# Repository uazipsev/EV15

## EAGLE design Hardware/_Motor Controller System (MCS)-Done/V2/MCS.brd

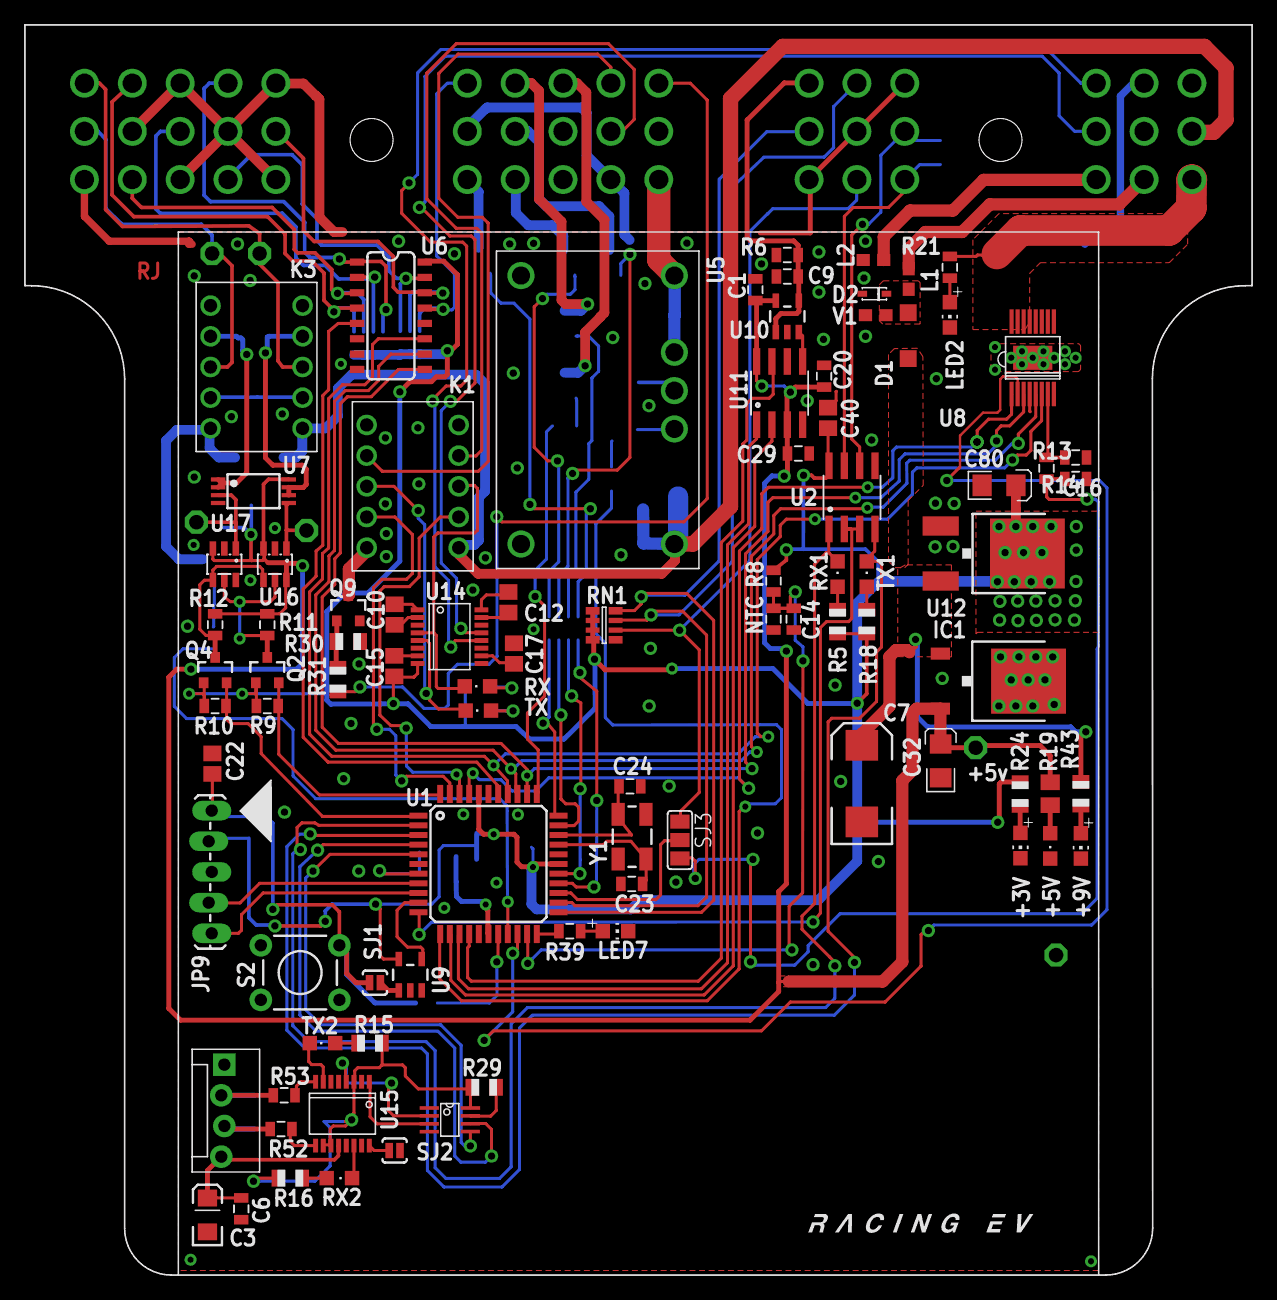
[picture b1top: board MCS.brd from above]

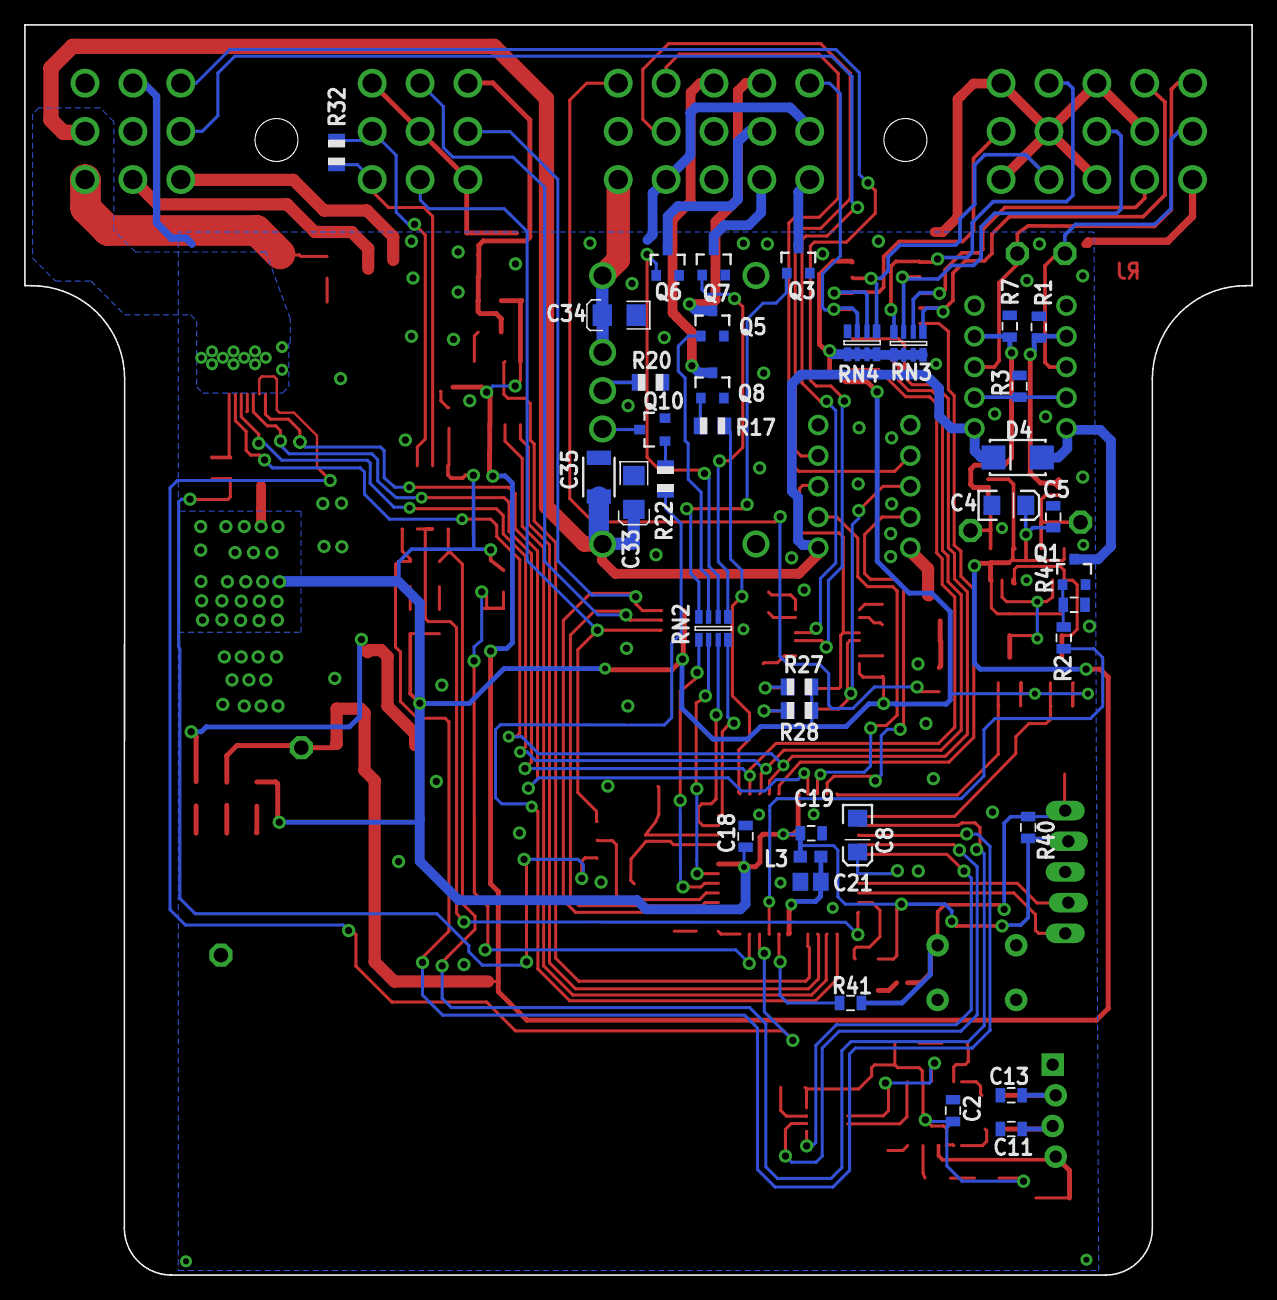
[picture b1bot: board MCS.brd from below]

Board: 2 copper layers, 101.6 x 103.5 mm, 133 parts (37 on the bottom side), 126 nets.

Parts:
+3V, +9V: CHIP-LED0805
+5V: Green; CHIPLED_0805
C1, C5, C14, C18, C19, C20, C29: 0.1uF; 0805
C2, C6: 0.1uf; 0805
C3: 4.7uF; EIA3216
C4, C8: 10uF; EIA3216
C7: 100uF; EIA7343
C9, C16: 10pF; 0805
C10, C12, C15, C17, C40: .1uF; C0805
C11, C13: 47pf; 0805
C21: 100n; C0805
C22: 10n; C0805
C23, C24: 12pF; 0805
C32, C33, C34, C80: 10uF; POLC1206
C35: 1uf; 1210
CASE2: 581-01-48-009
D1: 1N4001; SOD123
D2: MM5Z30; SOD-523F
D4: SMA-DIODE_ALT
IC1: 7805DT; TO252
JP9: ICSP; 1X05_LOCK_LONGPADS
JP13: MOLEX-1X4_LOCK
K1, K3: TQ2-2M-24V
L1, L2, L3: FB; 0603
LED2, LED7: CHIP-LED0805
NTC: 0805
Q1, Q2, Q3, Q4, Q5, Q6, Q7, Q8, Q9, Q10: BSS123; SOT23-3
R1, R6, R7, R8, R11, R12, R13, R14, R40: 10k; 0805
R2: 1k; 0805
R3: 100; 0805
R4: 100k; 0805
R5, R15, R17, R22, R27, R29, R31: 1K; R0805
R9, R10: 2k; 0805
R16, R18, R28: 1k; R0805
R19: 1K; M0805
R20: 383k; R0805
R21: 3.3k; 0805
R24: 499; R0805
R30: 10K; R0805
R32: 120; R0805
R39, R41: 499; 0805
R43: 1.2k; R0805
R52, R53: 27; 0805
RN1, RN2, RN3, RN4: RN-4; CRA06S
RX, RX2: CHIPLED_0805
RX1: RED; CHIPLED_0805
S2: ts; TACTILE-PTH
SJ1: SJ-NO; SJ_2S-NO
SJ2: PAD-JUMPER-2-NO_YES_SILK
SJ3: PAD-JUMPER-3-NO_YES_SILK_FULL_BOX
TP1, TP2, TP3, TP4, TP5, TP8: TESTPOINT; 4952
TX, TX2: CHIPLED_0805
TX1: GREEN; CHIPLED_0805
U1: DSPIC33FJ128GP804; TQFP-44
U2: SN75HVD08DR; SO-8
U4: SN74LVC2G241DCTR; VFSOP-8
U5: PTN78060HAH
U6: SN74HC251_SMD; SO016
U7: LM158; TSSOP-08
U8: VND7040AJTR-E; SSO-16-POWER
U9: MAX823; SOT23-5L
U10: OPA344; SOT23-5
U11: X9015_DIGI_POTS; SO08
U12: NCP1117DT33T5G; V-REG_DPACK
U14: ADM3101E; SSOP-16
U15: FT230X; SSOP-16
U16, U17: MCP4725; SOT23-6
U$1: LOGOM; L-M
U$2: INDPK1; PICKIT-PIN-1
V1: 13Vdc; 0603
Y1: 12Mhz; CRYSTAL-SMD-5X3

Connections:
3V: C2.1, R15.2, R16.2, R29.2, U4.8, U15.3, U15.10, U15.11
12V-EN: R22.1, U1.12
!CS: U1.15, U11.7
!RST: U1.20, U8.2
+: CASE2.45, L1.1
+3V3: C15.2, C18.1, C19.1, C40.1, C80.1, JP9.2, L3.2, Q2.1, Q4.1, R5.2, R8.2, R9.2, R10.2, R18.2, R24.2, R27.2, R28.2, R40.2, RN1.1, RN1.2, RN1.3, RN1.4, RN3.5, RN3.6, RN3.7, RN3.8, RN4.6, RN4.7, RN4.8, U1.28, U1.40, U2.8, U6.16, U9.5, U12.4, U14.8
+5V: C1.1, C4.A, C5.1, C20.1, C29.1, C32.1, IC1.2, R11.2, R12.2, R19.1, TP2.P$1, U7.8, U10.5, U11.3, U11.8, U16.3, U16.6, U17.3
+9V: C7.A, D1.C, IC1.1, R43.2, U12.3
+12V: C34.1, CASE2.30, U5.5, U5.6
+24V: C33.1, C35.1, CASE2.47, D4.C, K1.1, K3.1, U5.2, U8.EP
-: CASE2.42, L2.1
A: U1.37, U6.11, U8.6
ASEN: C16.1, R14.2, SJ3.3
B: U1.36, U6.10, U8.5
BOX_TEMP: C14.1, NTC.2, R8.1, U1.21
C: U1.35, U6.9, U8.3
DAC-EN: R2.2, U1.19
FAN: CASE2.48, R21.2, U8.13, U8.14, U8.15, U8.16
FAN-PWM: U1.41, U8.1
GND: +3V.C, +5V.C, +9V.C, C1.2, C2.2, C3.C, C4.C, C5.2, C6.2, C7.C, C8.C, C9.2, C11.2, C13.2, C14.2, C16.2, C17.1, C18.2, C19.2, C20.2, C21.2, C22.2, C23.2, C24.2, C29.2, C32.2, C33.2, C34.2, C35.2, C40.2, C80.2, CASE2.3, CASE2.5, CASE2.7, CASE2.9, CASE2.11, CASE2.13, CASE2.15, CASE2.17, CASE2.27, CASE2.33, CASE2.35, CASE2.37, CASE2.43, D2.A, IC1.3, JP9.3, JP13.1, L2.2, LED2.C, LED7.C, NTC.1, Q1.2, Q3.2, Q5.2, Q6.2, Q7.2, Q8.2, Q9.2, Q10.2, R1.2, R3.2, R4.1, R6.1, R7.2, R13.1, R20.1, R30.2, S2.1, SJ2.1, TP1.P$1, U1.6, U1.16, U1.29, U1.39, U2.5, U4.1, U4.4, U5.1, U5.7, U6.7, U6.8, U7.4, U8.4, U9.2, U10.2, U11.4, U11.6, U12.1, U14.9, U15.5, U15.13, U16.2, U17.2, U17.6, V1.1
INC: U1.14, U11.1
MC1-B: RN2.3, U1.32
MC1-F: RN2.1, U1.26
MC1-PE: RN2.4, U1.33
MC1-R: RN2.2, U1.27
MC1-RE: R17.1, U1.34
MC-1-B: CASE2.2, K3.8, TP4.P$1
MC-1-T: CASE2.1, K3.3, TP5.P$1
MC-PG-EN: CASE2.28, R31.1
MCRX: K1.3, RX.C, U14.4
MCTX: K1.8, TX.C, U14.5
unnamed: C22.1, JP9.1, R40.1, R41.1, S2.3, SJ1.2
unnamed: C21.1, L3.1, U1.17
unnamed: K3.7, R1.1, U7.1, U7.2
unnamed: C8.A, U1.7
unnamed: R39.2, U1.22
unnamed: +9V.A, R43.1
unnamed: Q3.1, RN2.8
unnamed: R41.2, U1.18
unnamed: CASE2.18, Q3.3
unnamed: SJ1.1, U9.1
unnamed: R15.1, TX2.A
unnamed: JP9.4, U1.8
unnamed: TX2.C, U15.7
unnamed: RX2.C, U15.14
unnamed: JP9.5, U1.9
unnamed: R16.1, RX2.A
unnamed: TP3.P$1, U7.5, U16.1
unnamed: K3.4, R7.1, U7.6, U7.7
unnamed: U4.2, U15.4
unnamed: Q5.1, RN2.7
unnamed: K3.2, K3.9, R3.1
unnamed: TP8.P$1, U7.3, U17.1
unnamed: LED2.A, R21.1
unnamed: U10.3, U11.5
unnamed: +3V.A, R24.1
unnamed: CASE2.19, Q5.3
unnamed: U4.3, U15.1
unnamed: R52.2, U15.9
unnamed: Q6.1, RN2.6
unnamed: CASE2.20, Q6.3
unnamed: R18.1, TX1.A
unnamed: R5.1, RX1.A
unnamed: SJ3.2, U1.25
unnamed: Q8.1, R17.2
unnamed: LED7.A, R39.1
unnamed: C24.1, U1.31, Y1.3
unnamed: C23.1, U1.30, Y1.1
unnamed: +5V.A, R19.2
unnamed: Q1.1, R2.1, R4.2
unnamed: D4.A, K3.10, Q1.3
unnamed: R13.2, R14.1, U8.7
unnamed: R53.2, U15.8
unnamed: C11.1, JP13.3, R52.1
unnamed: C10.1, U14.1
unnamed: C13.1, JP13.2, R53.1
unnamed: SJ2.2, U15.16
unnamed: D1.A, D2.C, L1.2, V1.2
unnamed: C10.2, U14.2
unnamed: C12.1, U14.16
unnamed: C12.2, U14.15
unnamed: C15.1, U14.7
unnamed: R29.1, U4.7
unnamed: CASE2.21, Q7.3
unnamed: CASE2.22, Q8.3
unnamed: C17.2, U14.10
unnamed: CASE2.40, U14.12
unnamed: CASE2.41, U14.13
unnamed: R27.1, RX.A
unnamed: R28.1, TX.A
unnamed: K1.10, Q9.3
unnamed: Q9.1, R30.1, R31.2
unnamed: R20.2, U5.4
unnamed: Q10.3, U5.3
unnamed: Q7.1, RN2.5
unnamed: Q10.1, R22.2
unnamed: C3.A, C6.1, JP13.4, U15.12
OUT: U1.38, U6.5
OUT-RX: CASE2.26, K1.4
OUT-TX: CASE2.25, K1.7
PUMP_OUTPUT_CONTROL: C9.1, CASE2.31, R6.2, U10.1, U10.4
RS-A: CASE2.38, R32.1, U2.6
RS-B: CASE2.39, R32.2, U2.7
RX2: K1.2, U1.42
RX3: U1.4, U4.6
RXD1: RX1.C, U1.2, U2.1
SCL: Q2.2, R9.1, U1.44
SCL_5V: Q2.3, R11.1, U16.5, U17.5
SDA: Q4.2, R10.1, U1.1
SDA_5V: Q4.3, R12.1, U16.4, U17.4
SP1: CASE2.4, RN3.1, U6.4
SP2: CASE2.6, RN3.2, U6.3
SP3: CASE2.8, RN3.3, U6.2
SP4: CASE2.10, RN3.4, U6.1
SP5: CASE2.12, RN4.1, U6.15
SP6: CASE2.14, RN4.2, U6.14
SP7: CASE2.16, RN4.3, U6.13
TEMP1: CASE2.32, RN1.8, U1.23
TEMP2: CASE2.34, RN1.7, U1.24
TEMP3: CASE2.36, RN1.6, SJ3.1
TX2: K1.9, U1.43
TX3: U1.5, U4.5
TXD1: TX1.C, U1.3, U2.4
U5-RE/DE: U1.11, U2.2, U2.3
UP/!DN: U1.13, U11.2
WDI: U1.10, U9.4

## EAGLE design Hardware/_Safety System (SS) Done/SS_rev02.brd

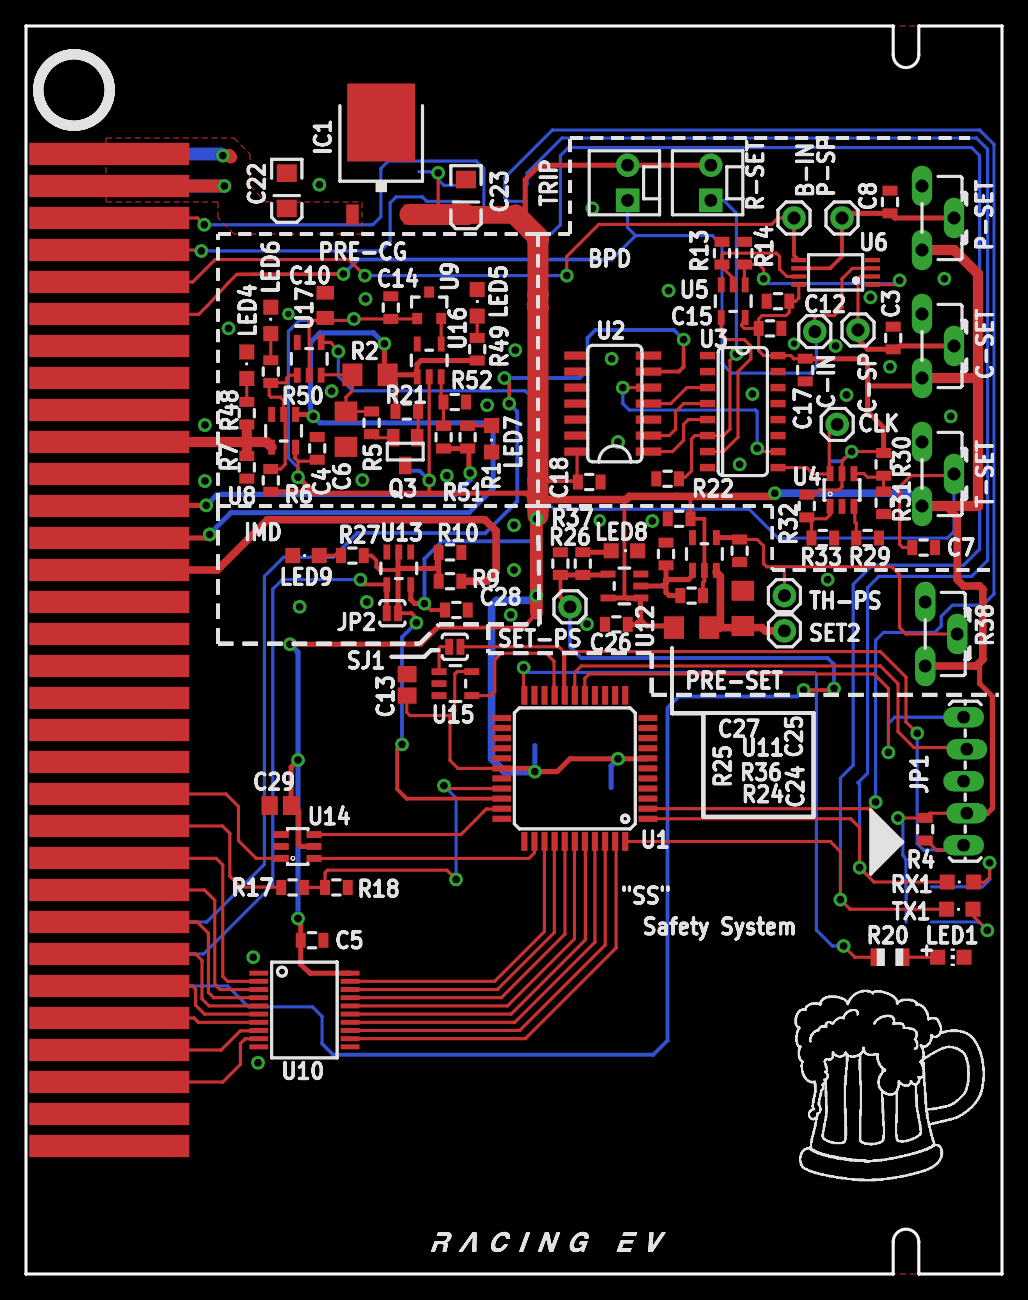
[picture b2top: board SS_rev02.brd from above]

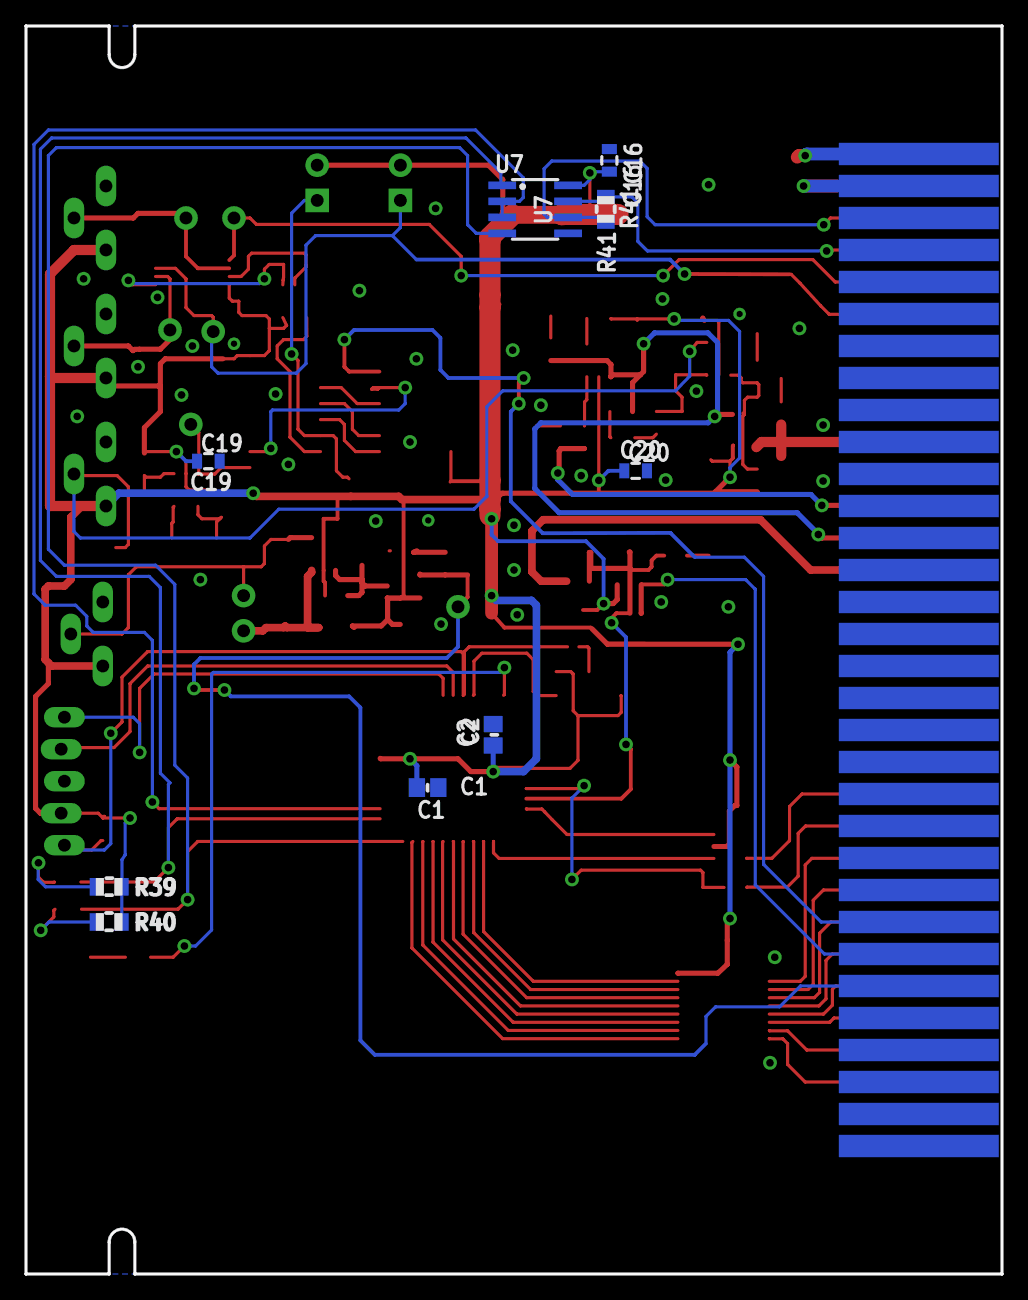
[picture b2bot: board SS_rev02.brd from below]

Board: 2 copper layers, 77.5 x 99.1 mm, 109 parts (9 on the bottom side), 78 nets.

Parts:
B-IN: TP; 1X01
C1, C2: .1uF; C0805
C3, C5, C7, C8, C20, C25: 1.0uF; 0805
C4, C14, C16, C26, C27, C28: 0.1uF; 0805
C6, C24: 100uF; 1206
C10: 0.1uF; C0805K
C12, C15, C17, C18, C19: 0.1uf; 0805
C13, C29: 0.1uF; C0805
C22, C23: 10uF; EIA3216
C-IN: TP; 1X01
C-SP: TP; 1X01
CARD1: CARD; CARD-64
CLK: TP; 1X01
IC1: 7805DT; TO252
JP1: 1X05_LOCK_LONGPADS
JP2: SJ_2S-NO
JP11: BPR; MOLEX-1X2_LOCK
JP21: Trigger; MOLEX-1X2_LOCK
LED1: CHIP-LED0805
LED4, LED5, LED6, LED7, LED8, LED9: CHIPLED_0805
P-SP: TP; 1X01
Q3: MMBT4403; SOT23
R1, R26, R48, R49: 2.0k; 0805
R2, R24: 115k; 1206
R3, R11, R12, R38: CA6H
R4, R13, R14, R18, R22: 10k; 0805
R5: 5; 0805
R6, R7, R25, R36, R37: 2.7k; 0805
R9, R10: 5k; 0805
R17: 22k; 0805
R20, R40: 1k; R0805
R21, R27, R32, R33: 1k; 0805
R29: 92k 1%; 0805
R30: 976k 1%; 0805
R31: 182k 1%; 0805
R39: 1K; R0805
R41: 120; R0805
R50: 1.0k; 0805
R51: 20k; 0805
R52: 28k; 0805
RX1: RED; CHIPLED_0805
SET2: RC-PS; 1X01
SET-PS: TP; 1X01
SJ1: SJ_2S-NO
TH-PS: TP; 1X01
TX1: GREEN; CHIPLED_0805
U1: PIC18F45K22; TQFP-44
U2: SN74HC21DR; SO14
U3: CD4015BM96; SO-16
U4: LTC6991; TSOT-23-6
U5: NC7SZ08P5X; SOT23-5
U6: LM358; TSSOP-8
U7: SN75HVD08DR; SO-8
U8: SN74AHC1G08; SOT23-5
U9: ISL21080; SOT-23
U10: MAX6818; SSOP-20
U11, U16, U17: MCP6541T-E/OT; SOT23-5
U12: SN74LVC1G132DBVR; SOT23-5
U13: NC7S14M5X; SOT23-5
U14: MAX6817EUT+T; SOT23-6
U15: MAX823; SOT23-5L
U$1: INDPK1; PICKIT-PIN-1
U$2: BEERM; B-M
U$3: LOGOM; L-M

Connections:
+5V: C1.1, C2.1, C4.1, C5.1, C10.1, C12.1, C13.1, C14.1, C15.1, C16.1, C17.1, C18.1, C19.1, C20.1, C23.A, C26.1, C27.1, C28.1, C29.1, IC1.2, JP1.2, JP11.2, JP21.2, R3.E, R4.2, R6.2, R11.E, R12.E, R24.1, R30.2, R32.2, R36.2, R38.E, R39.2, R40.2, U1.7, U1.28, U2.14, U3.16, U4.5, U5.5, U6.8, U7.8, U8.5, U9.1, U10.20, U11.2, U12.1, U12.5, U13.5, U14.5, U15.5, U16.2, U17.2
+9V: C22.A, CARD1.1, CARD1.2, CARD1.33, CARD1.34, IC1.1
AMD: CARD1.28, U10.7
AMD_O: U1.41, U10.14
AUX_O: U1.32, U14.4
BOTS: CARD1.29, U10.8
BOTS_O: U1.42, U10.13
BPD: CARD1.23, U10.2
BPD-R-SET: CARD1.57, U2.6
BPD_O: U1.36, U10.19
BRAKE_PRESURE: B-IN.1, CARD1.5, U6.5
CURRENT_SENSOR: C-IN.1, CARD1.6, JP21.1, U6.3
ECU: CARD1.30, U10.9
ECU_O: U1.43, U10.12
GND: C1.2, C2.2, C3.2, C4.2, C5.2, C6.2, C7.2, C8.2, C10.2, C12.2, C13.2, C14.2, C15.2, C16.2, C17.2, C18.2, C19.2, C20.2, C22.C, C23.C, C24.2, C25.2, C26.2, C27.2, C28.2, C29.2, CARD1.31, CARD1.32, CARD1.63, CARD1.64, IC1.3, JP1.3, LED1.C, LED4.C, LED5.C, LED6.C, LED7.C, LED8.C, LED9.C, Q3.3, R3.A, R7.1, R10.1, R11.A, R12.A, R13.2, R14.2, R18.1, R22.1, R25.1, R29.2, R31.1, R33.1, R37.1, R38.A, R52.2, U1.6, U1.29, U2.7, U3.8, U4.2, U5.3, U6.4, U7.5, U8.3, U9.3, U10.1, U10.10, U11.5, U12.3, U13.3, U14.2, U15.2, U16.5, U17.5
IMD: CARD1.24, U10.3
IMD-R-SET: CARD1.58, JP2.1, U13.4
IMD-SIG: CARD1.14, R9.2
IMD_O: U1.37, U10.18
IMD_STAT: JP2.2, R9.1, R10.2, R27.2, U1.31, U13.2
IS_O: R17.1, R18.2, U1.30
MAIN: CARD1.10, R7.2, R48.2, U8.4
unnamed: SJ1.1, U15.1
unnamed: CARD1.22, R17.2
unnamed: C25.1, R38.S, TH-PS.1, U11.4
unnamed: Q3.1, R21.2
unnamed: Q3.2, R5.1
unnamed: U2.5, U3.10
unnamed: C7.1, R3.S, U17.4
unnamed: R30.1, R31.2, U4.4
unnamed: U9.2, U16.4
unnamed: R51.2, R52.1, U16.3
unnamed: U3.7, U5.4
unnamed: JP11.1, R22.2, U3.6
unnamed: C24.1, R24.2, SET2.1, U11.3
unnamed: LED1.A, R20.1
unnamed: U2.1, U3.5
unnamed: U2.2, U3.4
unnamed: U2.4, U3.3
unnamed: R20.2, U1.22
unnamed: R29.1, U4.3
unnamed: CLK.1, U3.9, U4.6
unnamed: C8.1, P-SP.1, R12.S, U6.6
unnamed: R25.2, R36.1, U11.1, U12.2
unnamed: R32.1, R33.2, U4.1
unnamed: C3.1, C-SP.1, R11.S, U6.2
unnamed: R14.1, U5.1, U6.1
unnamed: LED8.A, R26.1
unnamed: R13.1, U5.2, U6.7
unnamed: LED9.A, R27.1
unnamed: LED7.A, R1.1
unnamed: R40.1, TX1.A
unnamed: JP1.4, U1.17
unnamed: R39.1, RX1.A
unnamed: JP1.5, U1.16
unnamed: JP1.1, R4.1, SJ1.2, U1.18
unnamed: C6.1, R2.2, R5.2, U17.3
unnamed: R6.1, R50.2, U8.2, U17.1
unnamed: LED4.A, R48.1
unnamed: LED5.A, R49.1
unnamed: LED6.A, R50.1
RELAY-SET: CARD1.59, R26.2, R37.2, SET-PS.1, U12.4
RS-A: CARD1.3, R41.1, U7.6
RS-B: CARD1.4, R41.2, U7.7
RTG: CARD1.12, R1.2, R51.1
RX1: RX1.C, U1.1, U7.1
SSW_C: CARD1.25, U10.4
SSW_C_O: U1.38, U10.17
SSW_L: CARD1.27, U10.6
SSW_L_O: U1.40, U10.15
SSW_R: CARD1.26, U10.5
SSW_R_O: U1.39, U10.16
START: CARD1.13, R2.1, R21.1, R49.2, U8.1, U16.1
TSMS: CARD1.21, U14.1
TSMS_O: U1.35, U14.6
TX1: TX1.C, U1.44, U7.4
U7-RE/DE: U1.2, U7.2, U7.3
WDT: U1.19, U15.4

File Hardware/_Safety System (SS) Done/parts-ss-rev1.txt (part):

Partlist

Exported from SS_rev02.brd at 5/4/2015 10:27:40 AM

EAGLE Version 7.2.0 Copyright (c) 1988-2014 CadSoft

Assembly variant: 

Part     Value            Package            Library               Position (mil)        Orientation

B-IN     TP               1X01               SparkFun-Connectors   (2400 -600)           R180
C-IN     TP               1X01               SparkFun-Connectors   (2465 -955)           R180
C-SP     TP               1X01               SparkFun-Connectors   (2600 -950)           R0
C1       .1uF             C0805              adafruit              (1795 -2380)          MR0
C2       .1uF             C0805              adafruit              (1590 -2215)          MR90
C3       1.0uF            0805               SparkFun-Capacitors   (2710 -975)           R90
C4       0.1uF            0805               SparkFun-Passives     (910 -1320)           R90
C5       1.0uF            0805               SparkFun-Passives     (894 -2857)           R0
C6       100uF            1206               SparkFun-Capacitors   (1000 -1260)          R270
C7       1.0uF            0805               SparkFun-Passives     (2805 -1630)          R0
C8       1.0uF            0805               SparkFun-Capacitors   (2700 -550)           R90
C10      0.1uF            C0805K             adafruit              (935 -873)            R90
C12      0.1uf            0805               SparkFun-Passives     (2350 -860)           R180
C13      0.1uF            C0805              adafruit              (1191 -2059)          R90
C14      0.1uF            0805               SparkFun-Passives     (1140 -880)           R90
C15      0.1uf            0805               SparkFun-Passives     (2325 -945)           R0
C16      0.1uF            0805               SparkFun-Passives     (1227 -420)           MR90
C17      0.1uf            0805               SparkFun-Passives     (2435 -1075)          R270
C18      0.1uf            0805               SparkFun-Passives     (1760 -1425)          R0
C19      0.1uf            0805               SparkFun-Passives     (2480 -1360)          MR0
C20      1.0uF            0805               SparkFun-Passives     (1145 -1390)          MR0
C22      10uF             EIA3216            SparkFun-Capacitors   (815 -515)            R270
C23      10uF             EIA3216            SparkFun-Capacitors   (1375 -535)           R270
C24      100uF            1206               SparkFun-Capacitors   (2240 -1820)          R90
C25      1.0uF            0805               SparkFun-Passives     (2230 -1640)          R270
C26      0.1uF            0805               SparkFun-Passives     (1845 -1870)          R180
C27      0.1uF            0805               SparkFun-Passives     (2041 -1540)          R180
C28      0.1uF            0805               SparkFun-Passives     (1345 -1825)          R0
C29      0.1uF            C0805              adafruit              (795 -2436)           R180
CARD1    CARD             CARD-64            FSAE Eletric          (0 0)                 R270
CLK      TP               1X01               SparkFun-Connectors   (2535 -1245)          R0
IC1      7805DT           TO252              adafruit              (1110 -400)           R0
JP1                       1X05_LOCK_LONGPADS SparkFun-Connectors   (2930 -2560)          R90
JP2                       SJ_2S-NO           SparkFun-Passives     (1145 -1835)          R0
JP11     BPR              MOLEX-1X2_LOCK     SparkFun-Connectors   (2140 -540)           R90
JP21     Trigger          MOLEX-1X2_LOCK     SparkFun-Connectors   (1880 -540)           R90
LED1                      CHIP-LED0805       adafruit              (2890 -2910)          R270
LED4                      CHIPLED_0805       adafruit              (690 -1060)           R0
LED5                      CHIPLED_0805       adafruit              (1410 -865)           R0
LED6                      CHIPLED_0805       adafruit              (765 -920)            R0
LED7                      CHIPLED_0805       adafruit              (1455 -1290)          R180
LED8                      CHIPLED_0805       adafruit              (1870 -1640)          R270
LED9                      CHIPLED_0805       adafruit              (875 -1655)           R90
P-SP     TP               1X01               SparkFun-Connectors   (2550 -600)           R90
Q3       MMBT4403         SOT23              SparkFun-DiscreteSemi (1185 -1330)          R180
R1       2.0k             0805               SparkFun-Passives     (1380 -1285)          R270
R2       115k             1206               SparkFun-Resistors    (1075 -1090)          R180
R3                        CA6H               pot                   (2800 -1400)          R270
R4       10k              0805               SparkFun-Passives     (2810 -2510)          R90
R5       5                0805               SparkFun-Passives     (1080 -1240)          R90
R6       2.7k             0805               SparkFun-Passives     (765 -1420)           R270
R7       2.7k             0805               SparkFun-Passives     (690 -1379)           R90
R9       5k               0805               SparkFun-Passives     (1325 -1735)          R0
R10      5k               0805               SparkFun-Passives     (1325 -1645)          R180
R11                       CA6H               pot                   (2800 -1000)          R270
R12                       CA6H               pot                   (2800 -600)           R270
R13      10k              0805               SparkFun-Resistors    (2175 -710)           R90
R14      10k              0805               SparkFun-Resistors    (2245 -710)           R90
R17      22k              0805               SparkFun-Passives     (833 -2692)           R180
R18      10k              0805               SparkFun-Passives     (970 -2692)           R180
R20      1k               R0805              adafruit              (2700 -2910)          R180
R21      1k               0805               SparkFun-Passives     (1190 -1205)          R0
R22      10k              0805               SparkFun-Resistors    (2005 -1415)          R0
R24      115k             1206               SparkFun-Resistors    (2080 -1880)          R0
R25      2.7k             0805               SparkFun-Passives     (2000 -1650)          R270
R26      2.0k             0805               SparkFun-Passives     (1740 -1680)          R270
R27      1k               0805               SparkFun-Passives     (1020 -1655)          R0
R29      92k 1%           0805               SparkFun-Resistors    (2630 -1600)          R0
R30      976k 1%          0805               SparkFun-Resistors    (2680 -1370)          R90
R31      182k 1%          0805               SparkFun-Resistors    (2680 -1490)          R90
R32      1k               0805               SparkFun-Resistors    (2440 -1500)          R90
R33      1k               0805               SparkFun-Resistors    (2490 -1600)          R180
R36      2.7k             0805               SparkFun-Passives     (2080 -1780)          R0
R37      2.7k             0805               SparkFun-Passives     (1670 -1680)          R270
R38                       CA6H               pot                   (2810 -1900)          R270
R39      1K               R0805              adafruit              (2790 -2690)          MR0
R40      1k               R0805              adafruit              (2790 -2800)          MR0
R41      120              R0805              adafruit              (1238 -573)           MR90
R48      2.0k             0805               SparkFun-Passives     (690 -1210)           R270
R49      2.0k             0805               SparkFun-Passives     (1410 -1010)          R270
R50      1.0k             0805               SparkFun-Passives     (765 -1080)           R270
R51      20k              0805               SparkFun-Resistors    (1305 -1285)          R90
R52      28k              0805               SparkFun-Resistors    (1340 -1175)          R0
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
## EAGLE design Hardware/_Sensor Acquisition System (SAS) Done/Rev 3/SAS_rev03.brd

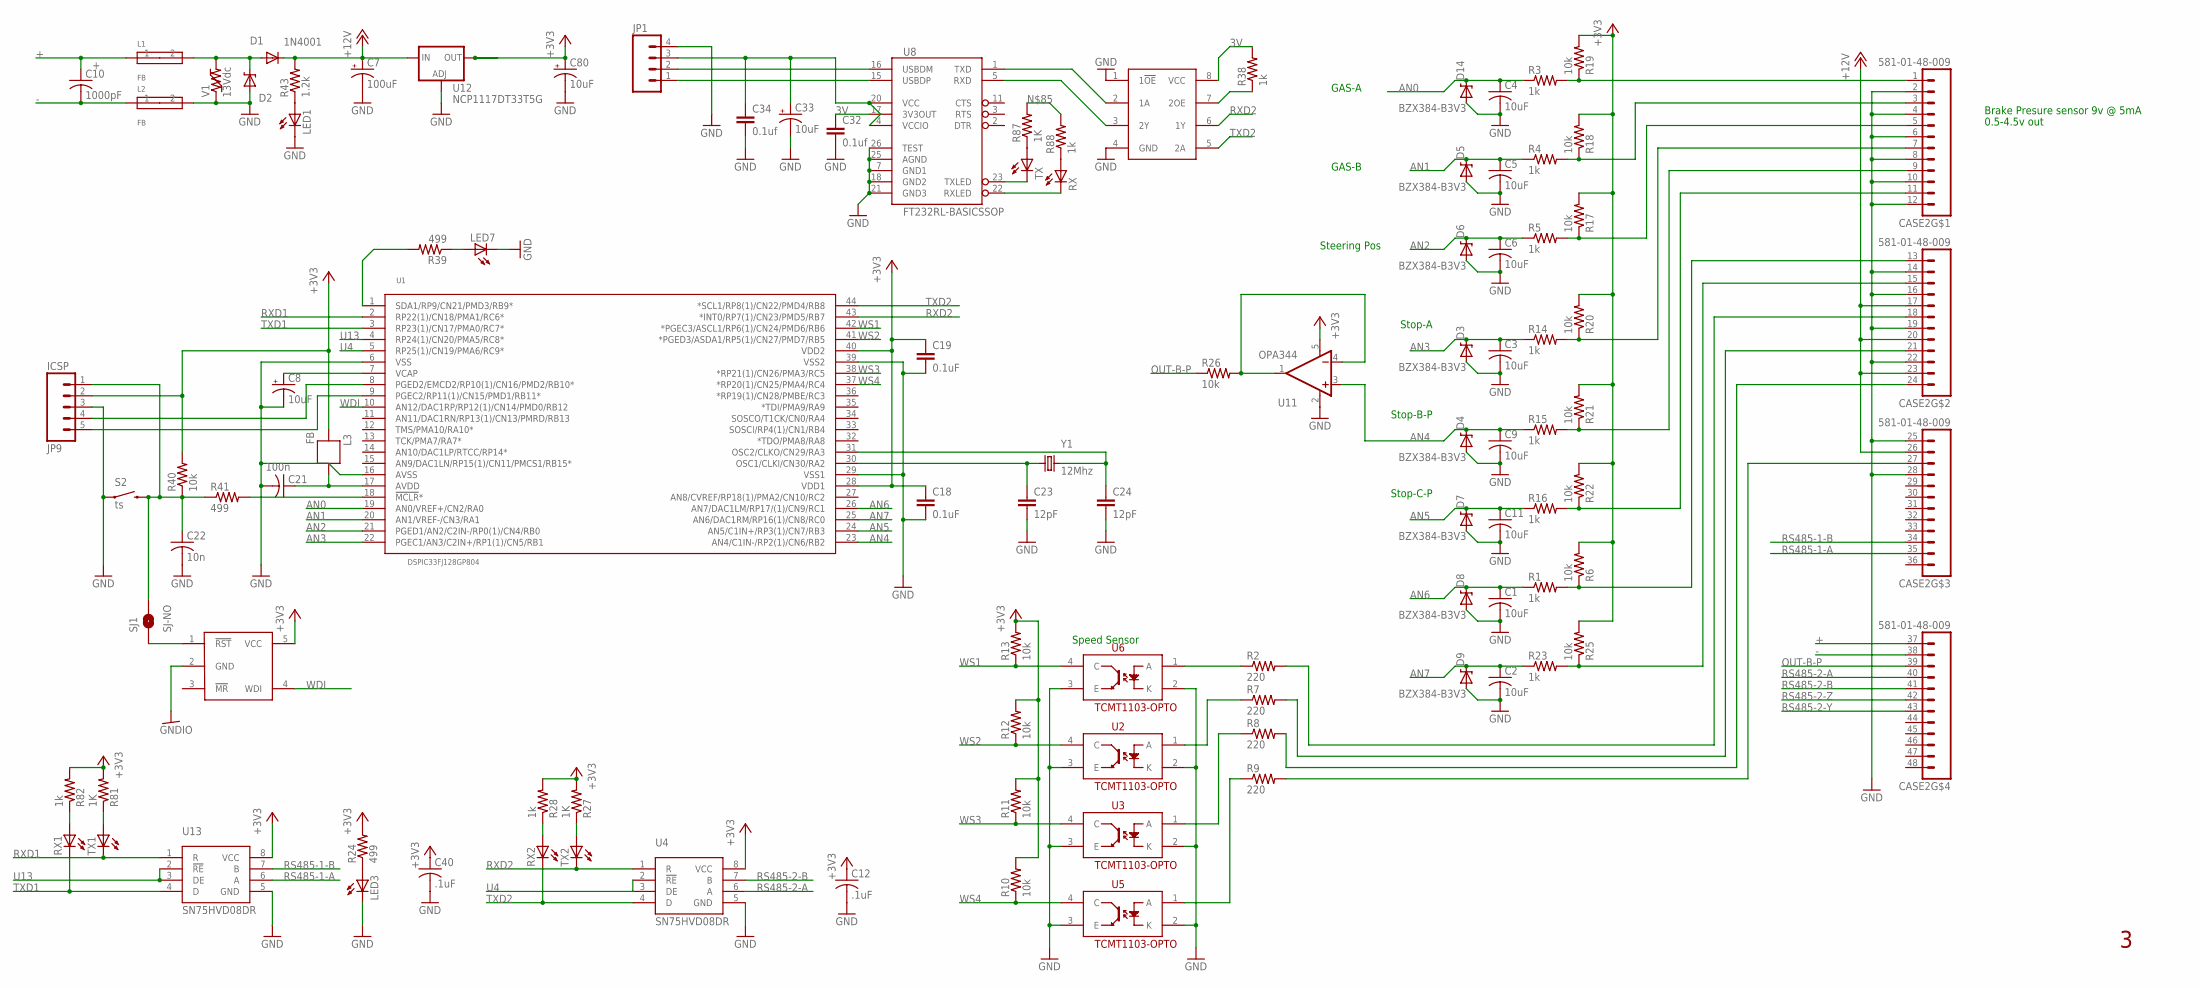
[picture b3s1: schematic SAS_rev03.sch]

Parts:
C1, C2, C3, C4, C5, C6, C9, C11: 10uF; C0805
C7: 100uF; EIA7343
C8, C33: 10uF; EIA3216
C10: 1000pF; C1825
C12, C40: .1uF; C0805
C18, C19: 0.1uF; 0805
C21: 100n; C0805
C22: 10n; C0805
C23, C24: 12pF; 0805
C32, C34: 0.1uf; 0805
C80: 10uF; POLC1206
CASE2: 581-01-48-009
D1: 1N4001; SOD123
D2: MM5Z30; SOD-523F
D3, D4, D5, D6, D7, D8, D9, D14: BZX384-B3V3; SOD-323
JP1: M04POLAR; MOLEX-1X4
JP9: ICSP; 1X05_LOCK_LONGPADS
L1, L2, L3: FB; 0603
LED1, LED3, LED7: LEDCHIP-LED0805; CHIP-LED0805
R1, R3, R4, R5, R14, R15, R16, R23, R28, R38, R82, R88: 1k; R0805
R2, R7, R8, R9: 220; R0805
R6, R10, R11, R12, R13, R17, R18, R19, R20, R21, R22, R25, R26: 10k; R0805
R24: 499; R0805
R27, R81, R87: 1K; R0805
R39, R41: 499; 0805
R40: 10k; 0805
R43: 1.2k; R0805
RX, RX1, RX2: LEDCHIPLED_0805; CHIPLED_0805
S2: ts; TACTILE-PTH
SJ1: SJ-NO; SJ_2S-NO
TX, TX1, TX2: LEDCHIPLED_0805; CHIPLED_0805
U1: DSPIC33FJ128GP804; TQFP-44
U2, U3, U5, U6: TCMT1103-OPTO; SSOP-4
U4, U13: SN75HVD08DR; SO-8
U8: FT232RL-BASICSSOP; SSOP28DB
U9: MAX823; SOT23-5L
U11: OPA344; SOT23-5
U12: NCP1117DT33T5G; V-REG_DPACK
U14: SN74LVC2G241DCTR; VFSOP-8
V1: 13Vdc; 0603
Y1: 12Mhz; CRYSTAL-SMD-5X3

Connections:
3V: C32.1, R38.2, U8.17 (3V3OUT), U14.8 (VCC)
+: C10.1, CASE2.37 (1), L1.1
+3V3: C12.1, C18.1, C19.1, C40.1, C80.1 (+), JP9.2, L3.2, R6.2, R10.2, R11.2, R12.2, R13.2, R17.2, R18.2, R19.2, R20.2, R21.2, R22.2, R24.2, R25.2, R27.2, R28.2, R40.2, R81.2, R82.2, U1.28 (VDD1), U1.40 (VDD2), U4.8 (VCC), U9.5 (VCC), U11.5 (V+), U12.4 (OUT), U13.8 (VCC)
+12V: C7.A (+), CASE2.17 (5), CASE2.20 (8), CASE2.23 (11), CASE2.26 (2), D1.C, R43.2, U12.3 (IN)
-: C10.2, CASE2.38 (2), L2.1
AN0: C4.1, D14.1 (C), R3.1, U1.19 (AN0/VREF+/CN2/RA0)
AN1: C5.1, D5.1 (C), R4.1, U1.20 (AN1/VREF-/CN3/RA1)
AN2: C6.1, D6.1 (C), R5.1, U1.21 (PGED1/AN2/C2IN-/RP0(1)/CN4/RB0)
AN3: C3.1, D3.1 (C), R14.1, U1.22 (PGEC1/AN3/C2IN+/RP1(1)/CN5/RB1)
AN4: C9.1, D4.1 (C), R15.1, U1.23 (AN4/C1IN-/RP2(1)/CN6/RB2), U11.3 (+IN)
AN5: C11.1, D7.1 (C), R16.1, U1.24 (AN5/C1IN+/RP3(1)/CN7/RB3)
AN6: C1.1, D8.1 (C), R1.1, U1.26 (AN7/DAC1LM/RP17/(1)/CN9/RC1)
AN7: C2.1, D9.1 (C), R23.1, U1.25 (AN6/DAC1RM/RP16(1)/CN8/RC0)
GHT: D1.A, D2.C, L1.2, V1.2
GND: C1.2, C2.2, C3.2, C4.2, C5.2, C6.2, C7.C (-), C8.C (-), C9.2, C11.2, C12.2, C18.2, C19.2, C21.2, C22.2, C23.2, C24.2, C32.2, C33.C (-), C34.2, C40.2, C80.2 (-), CASE2.2, CASE2.4, CASE2.6, CASE2.8, CASE2.10, CASE2.12, CASE2.14 (2), CASE2.16 (4), CASE2.19 (7), CASE2.22 (10), CASE2.25 (1), CASE2.28 (4), D2.A, D3.2 (A), D4.2 (A), D5.2 (A), D6.2 (A), D7.2 (A), D8.2 (A), D9.2 (A), D14.2 (A), JP1.4, JP9.3, L2.2, LED1.C, LED3.C, LED7.C, S2.1, U1.6 (VSS), U1.16 (AVSS), U1.29 (VSS1), U1.39 (VSS2), U2.2 (K), U2.3 (E), U3.2 (K), U3.3 (E), U4.5 (GND), U5.2 (K), U5.3 (E), U6.2 (K), U6.3 (E), U8.7 (GND1), U8.18 (GND2), U8.21 (GND3), U8.25 (AGND), U8.26 (TEST), U11.2 (V-), U12.1 (ADJ), U13.5 (GND), U14.1 (1!OE), U14.4 (GND), V1.1
GNDIO: U9.2 (GND)
unnamed: C22.1, JP9.1, R40.1, R41.1, S2.3 (2), SJ1.2
unnamed: C21.1, L3.1, U1.17 (AVDD)
unnamed: CASE2.13 (1), R1.2, R6.1
unnamed: C8.A (+), U1.7 (VCAP)
unnamed: R39.2, U1.1 (SDA1/RP9/CN21/PMD3/RB9*)
unnamed: LED1.A, R43.1
unnamed: CASE2.1, R3.2, R19.1
unnamed: R41.2, U1.18 (!MCLR!*)
unnamed: CASE2.15 (3), R23.2, R25.1
unnamed: SJ1.1, U9.1 (!RST)
unnamed: CASE2.18 (6), R2.2
unnamed: JP9.4, U1.8 (PGED2/EMCD2/RP10(1)/CN16/PMD2/RB10*)
unnamed: CASE2.3, R4.2, R18.1
unnamed: CASE2.5, R5.2, R17.1
unnamed: JP9.5, U1.9 (PGEC2/RP11(1)/CN15/PMD1/RB11*)
unnamed: CASE2.21 (9), R7.2
unnamed: CASE2.24 (12), R8.2
unnamed: CASE2.27 (3), R9.2
unnamed: R2.1, U6.1 (A)
unnamed: R7.1, U2.1 (A)
unnamed: R8.1, U3.1 (A)
unnamed: R9.1, U5.1 (A)
unnamed: R26.2, U11.1 (OUT), U11.4 (-IN)
unnamed: LED3.A, R24.1
unnamed: CASE2.7, R14.2, R20.1
unnamed: CASE2.9, R15.2, R21.1
unnamed: CASE2.11, R16.2, R22.1
unnamed: R27.1, TX2.A
unnamed: R28.1, RX2.A
unnamed: R38.1, U14.7 (2OE)
unnamed: LED7.A, R39.1
unnamed: C24.1, U1.31 (OSC2/CLKO/CN29/RA3), Y1.3 (2)
unnamed: C23.1, U1.30 (OSC1/CLKI/CN30/RA2), Y1.1
unnamed: JP1.2, U8.16 (USBDM)
unnamed: JP1.1, U8.15 (USBDP)
unnamed: R87.1, TX.A
unnamed: R88.1, RX.A
unnamed: TX.C, U8.23 (TXLED)
unnamed: RX.C, U8.22 (RXLED)
unnamed: C33.A (+), C34.1, JP1.3, R87.2, R88.2, U8.4 (VCCIO), U8.20 (VCC)
unnamed: R81.1, TX1.A
unnamed: R82.1, RX1.A
unnamed: U8.1 (TXD), U14.2 (1A)
unnamed: U8.5 (RXD), U14.3 (2Y)
OUT-B-P: CASE2.39 (3), R26.1
RS485-1-A: CASE2.35 (11), U13.6 (A)
RS485-1-B: CASE2.34 (10), U13.7 (B)
RS485-2-A: CASE2.40 (4), U4.6 (A)
RS485-2-B: CASE2.41 (5), U4.7 (B)
RS485-2-Y: CASE2.43 (7)
RS485-2-Z: CASE2.42 (6)
RXD1: TX1.C, U1.2 (RP22(1)/CN18/PMA1/RC6*), U13.1 (R)
RXD2: TX2.C, U1.43 (*INT0/RP7(1)/CN23/PMD5/RB7), U4.1 (R), U14.6 (1Y)
TXD1: RX1.C, U1.3 (RP23(1)/CN17/PMA0/RC7*), U13.4 (D)
TXD2: RX2.C, U1.44 (*SCL1/RP8(1)/CN22/PMD4/RB8), U4.4 (D), U14.5 (2A)
U4: U1.5 (RP25(1)/CN19/PMA6/RC9*), U4.2 (!RE), U4.3 (DE)
U13: U1.4 (RP24(1)/CN20/PMA5/RC8*), U13.2 (!RE), U13.3 (DE)
WDI: U1.10 (AN12/DAC1RP/RP12(1)/CN14/PMD0/RB12), U9.4 (WDI)
WS1: R13.1, U1.42 (*PGEC3/ASCL1/RP6(1)/CN24/PMD6/RB6), U6.4 (C)
WS2: R12.1, U1.41 (*PGED3/ASDA1/RP5(1)/CN27/PMD7/RB5), U2.4 (C)
WS3: R11.1, U1.38 (*RP21(1)/CN26/PMA3/RC5), U3.4 (C)
WS4: R10.1, U1.37 (*RP20(1)/CN25/PMA4/RC4), U5.4 (C)

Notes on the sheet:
GAS-A
GAS-B
Steering Pos
Stop-A
Stop-B-P
Stop-C-P
Speed Sensor
Brake Presure sensor 9v @ 5mA
0.5-4.5v out

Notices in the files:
parts and their libraries:
SparkFun-Connectors: Licensing: CC v3.0 Share-Alike You are welcome to use this library for commercial purposes.
SparkFun-PowerIC: Licensing: Creative Commons ShareAlike 4.0 International - https://creativecommons.org/licenses/by-sa/4.0
